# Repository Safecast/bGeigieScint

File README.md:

# bGeigieScint

**bGeigieScint** is a compact radiation detection board featuring a Silicon Photomultiplier (SiPM) based sensor system with integrated high-voltage generation, analog signal processing, and USB connectivity.

## 📋 Features

- **Microcontroller**: ATSAML21G18B (ARM Cortex-M0+, 256KB Flash, 32KB RAM)
- **SiPM Interface**: Complete analog frontend with adjustable HV bias (30-70V)
- **Power Management**: Multi-rail power supply (3.3V, 3.0V, Vload, Vbias)
- **Connectivity**: USB-C interface with ESD protection
- **Debug**: 10-pin J-LINK SWD interface + 18 test points
- **Expansion**: Multiple GPIO headers for external interfaces
- **Compact**: 40mm × 100mm 4-layer PCB

## 🔧 Hardware Specifications

### Main Components

| Component | Part Number | Function |
|-----------|-------------|----------|
| MCU | ATSAML21G18B-AUT | Main microcontroller (48-pin QFN) |
| USB | USB3.1C16PFSMT | USB-C connector (USB 2.0) |
| LDO 3.3V | XC6209F332MR-G | Main 3.3V regulator |
| LDO 3.0V | TPS7A2030PDBVR | 3.0V rail for analog |
| LDO Vload | LT3014BHVES5 | Low-noise LDO for HV control |
| OpAmp | OPA357AIDBVR | Shaper amplifier |
| Comparator | TLV3201AIDBVT | Fast comparator |
| Latch | MC14043BDR2G | Digital latch for triggering |

### SiPM Sensor

- **Part Number**: AFBR-S4N44P014M (Broadcom)
- **Type**: NUV-HD Silicon Photomultiplier
- **Active Area**: 4×4 mm²
- **Spectral Range**: 350-900 nm (peak sensitivity ~420 nm)
- **Datasheet**: [AFBR-S4N44P014M Documentation](https://docs.broadcom.com/doc/AFBR-S4N44P014M-NUV-MT-Silicon-Photomultiplier)

### Scintillator Crystal

- **Material**: CsI(Tl) - Cesium Iodide doped with Thallium
- **Dimensions**: 10 mm × 10 mm × 20 mm
- **Emission Peak**: ~550 nm (matches SiPM sensitivity)
- **Application**: Gamma ray detection coupled to SiPM

### Power Supply

- **Input**: 4.5-6V via USB-C or external connector
- **Output Rails**:
  - 3.3V @ up to 200mA (digital)
  - 3.0V @ up to 100mA (analog)
  - Vload (adjustable)
  - Vbias: 30-70V @ low current (SiPM bias)

### HV Generation

The board features an integrated **boost converter + linear regulator** topology for SiPM bias generation:

- **Boost Stage**: PWM-controlled (L1 10mH inductor, Q3 P-FET, D9 Schottky)
- **Regulation**: LT3014 ultra-low-noise LDO
- **Control**: MCU DAC output (PA02_DAC_HV) sets target voltage
- **Monitoring**: Comparator feedback (PB10_HV_COMP_OUT)
- **Output**: Adjustable 30-70V Vbias for SiPM

## 📁 Project Structure

```
bGeigieScint/
├── bGeigieScint/
│   ├── bGeigieScint.kicad_pro       # KiCad project file
│   ├── bGeigieScint.kicad_sch       # Schematic (organized in functional blocks)
│   ├── bGeigieScint.kicad_pcb       # PCB layout (4-layer, 40×100mm)
│   ├── bGeigieScint-backups/        # Automatic backups
│   ├── firmware/                    # Firmware source code
│   │   └── PomeloCore/              # Main firmware project
│   ├── bootloader/                  # Bootloader files
│   │   └── uf2-samd21/              # UF2 bootloader for SAMD21
│   ├── v1_2/                        # Version 1.2 reference files
│   │   ├── schematic/               # V1.2 schematic PDF
│   │   ├── firmware/                # V1.2 firmware
│   │   └── bootloader/              # V1.2 bootloader
│   ├── Images/                      # Project images and photos
│   └── Misc Docs/                   # Additional documentation
├── BOM.csv                          # Bill of Materials
├── Python scripts (*.py)            # KiCad automation scripts
└── README.md                        # This file
```

## 🎨 Schematic Organization

The schematic is organized into **7 functional blocks**:

1. **USB & POWER INPUT**: USB-C interface, power connectors, reset button
2. **POWER MANAGEMENT**: LDOs, inductors, power distribution
3. **MCU CORE**: Microcontroller, crystal, decoupling
4. **ANALOG FRONTEND**: SiPM signal chain, opamps, comparators
5. **LOGIC & CONTROL**: Digital logic, latches, level shifters
6. **EXPANSION I/O**: Pin headers for external connections
7. **DEBUG & TEST**: J-LINK interface, test points

## 🔌 Pinout & Interfaces

### J-LINK Debug Header (10-pin)
```
1: VCC        2: SWDIO
3: GND        4: SWCLK
5: GND        6: SWO
7: NC         8: NC
9: GND       10: RESET
```

### Expansion Headers

- **H2, H3**: 7-pin GPIO expansion
- **H5**: 7-pin expansion with labeled signals
- **MEAS1**: 2-pin measurement header
- **P1, P2**: 2×2 power connectors (mirrored on Pomelo Physics board)

### Key Signals

| Signal | Description |
|--------|-------------|
| SiPM_A | SiPM analog input |
| Vbias | SiPM bias voltage output |
| SHAPER_OUT | Shaped pulse output |
| PA02_DAC_HV | HV control DAC output |
| PA10_PWM | Boost converter PWM |
| PB03_PEAKDET_EN | Peak detector enable |
| PA23_TRG_OUT | Trigger output |

## 📊 Version History

### V1.3 (Current)
**Major improvements over V1.2:**

✅ **Added (47 components)**:
- USB-C connector (USBC1)
- Reset button (BUT1)
- J-LINK debug header
- 18 test points (TP1-TP18)
- Additional transistors (Q4, Q5) and diodes (D6, D8, D10)
- 15 new resistors for better signal conditioning

✅ **Changed**:
- C44: 1uF → 4.7uF
- C45: 4.7uF → 1uF
- H2, H3: 6-pin → 7-pin headers (expanded)

✅ **Enhanced**:
- Better debugging capability
- Improved power filtering
- More flexible I/O expansion

### V1.2 (Legacy)
- Initial production version
- PDF schematic available in `v1_2/schematic/`

## 🚀 Getting Started

### Prerequisites

- **KiCad 9.0** or later
- Basic understanding of radiation detection and SiPM operation
- JTAG/SWD programmer (e.g., J-Link, ST-Link)

### Opening the Project

1. Clone this repository
2. Open `bGeigieScint/bGeigieScint.kicad_pro` in KiCad
3. The schematic shows functional blocks with dashed rectangles
4. The PCB has components organized by function

### Manufacturing

**PCB Specifications:**
- **Layers**: 4 (signal/GND/VCC/signal)
- **Dimensions**: 40mm × 100mm
- **Thickness**: 1.6mm
- **Copper**: 35μm (1oz) on all layers
- **Min Track/Space**: 0.15mm / 0.15mm (for 0805 components)
- **Finish**: HASL or ENIG recommended
- **Solder Mask**: Green (top and bottom)

**Assembly Notes:**
- Minimum component size: 0805 for passives
- QFN-48 MCU requires reflow soldering
- LDOs are SOT-23-5 packages
- Test points for easy debugging

## 📝 Design Notes

### Power Planes
- **Layer 1 (In1.Cu)**: GND plane - solid pour for low noise
- **Layer 2 (In2.Cu)**: VCC plane - split for 3.3V/3.0V rails

### Critical Traces
- Keep SiPM analog traces short and shielded
- HV traces (Vbias) should be isolated from digital signals
- Crystal traces should be short with GND guard ring

### Component Placement
Components are organized into functional blocks:
- Power supply on left side
- MCU in center
- Analog section on right
- Digital logic bottom-right

## 🔬 Applications

- Radiation detection and measurement
- Scintillation counting
- Environmental monitoring
- Educational radiation physics
- DIY Geiger counter replacement with better sensitivity

## 👥 Credits

**Original Designer**: Mihai Cuciuc (M. Cuciuc)
**Original Repository**: [github.com/mihaicuciuc/pomelo](https://github.com/mihaicuciuc/pomelo)
**Organization**: Safecast
**Date**: 2024-2025

Safecast appreciates the great work that Mihai has done and made publicly available. This project builds upon the original Pomelo design.

## 📄 License

- **Hardware Design** (schematics, PCB layouts, design files): [CC0 1.0 Universal](https://creativecommons.org/publicdomain/cc0/1.0/)
- **Firmware and Software**: [MIT License](https://opensource.org/licenses/MIT)

This project is completely open source and free to use, modify, and distribute.

## 🤝 Contributing

Contributions are welcome! Please:

1. Fork the repository
2. Create a feature branch
3. Make your changes
4. Submit a pull request

For major changes, please open an issue first to discuss what you would like to change.

## 📞 Support

- **Project Page**: [Pomelo on Crowd Supply](https://www.crowdsupply.com/pomelo-instrumentation/pomelo)
- **Safecast**: [https://safecast.org](https://safecast.org)
- Report issues through the repository's issue tracker

## ⚠️ Safety Warning

This board generates **high voltage** (up to 70V) for SiPM biasing. Handle with care:
- Do not touch HV traces while powered
- Use proper ESD protection
- Follow safe electronics handling practices
- Designed for educational and research purposes

---

**Made with ❤️ for the radiation detection community**

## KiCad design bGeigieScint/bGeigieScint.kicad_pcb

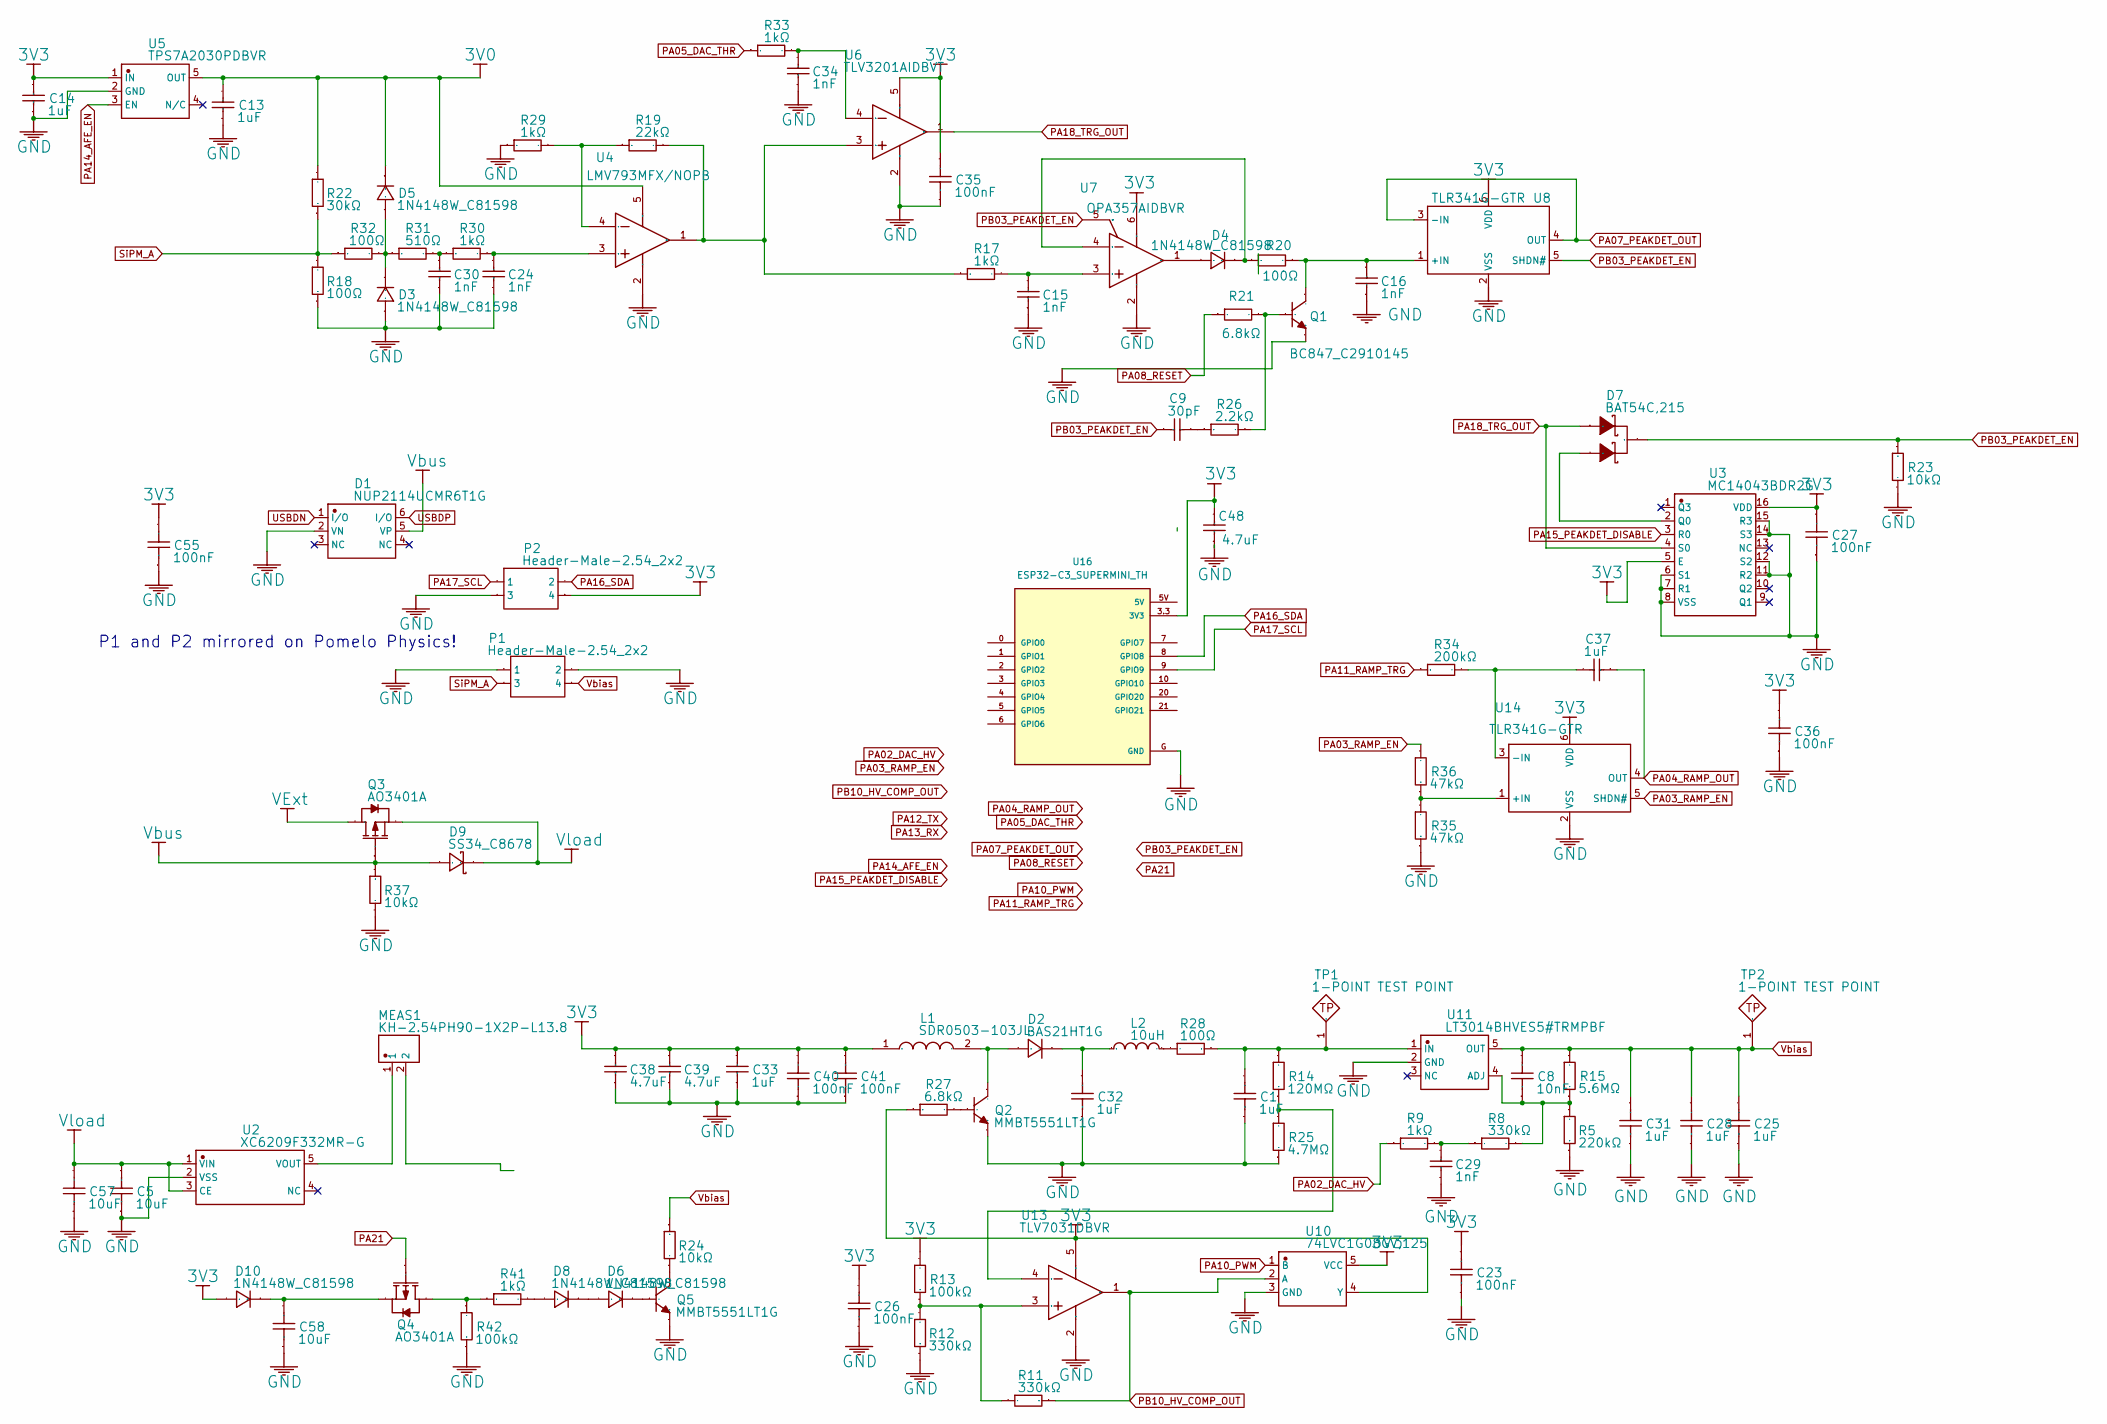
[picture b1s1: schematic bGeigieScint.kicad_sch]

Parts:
C1, C32: 1uF; C_0805_2012Metric; Manufacturer Part GRM55DR72D105KW01L
C5, C57, C58: 10uF; C_1206_3216Metric; Manufacturer Part CL10A106KP8NNNC
C8: 10nF; C_0805_2012Metric; Manufacturer Part 12062C103KAT2A
C9: 30pF; C_0805_2012Metric; Manufacturer Part 0603CG300J500NT
C13, C14, C33, C37: 1uF; C_0805_2012Metric; Manufacturer Part CL10A105KB8NNNC
C15, C16, C24, C29, C30, C34: 1nF; C_0805_2012Metric; Manufacturer Part CL10B102KB8NNNC
C23, C26, C27, C35, C36, C40, C41, C55: 100nF; C_0805_2012Metric; Manufacturer Part CC0603KRX7R9BB104
C25, C28, C31: 1uF; C_0805_2012Metric; Manufacturer Part 08051C105KAT2A
C38, C39: 4.7uF; C_1812_4532Metric; Manufacturer Part 1206B475K500NT
C48: 4.7uF; C_0805_2012Metric; Manufacturer Part CL10A475KO8NNNC
D1: NUP2114UCMR6T1G; SO-8_3.9x4.9mm_P1.27mm; Manufacturer Part NUP2114UCMR6T1G
D2: BAS21HT1G; SOT-23; Manufacturer Part BAS21HT1G
D3, D4, D5, D6, D8, D10: 1N4148W_C81598; D_SOD-123; Manufacturer Part 1N4148W
D7: BAT54C,215; SOT-23; Manufacturer Part BAT54C,215
D9: SS34_C8678; D_SMA; Manufacturer Part SS34
L1: SDR0503-103JL; L_0805_2012Metric
L2: 10uH; L_1210_3225Metric; Manufacturer Part SDFL1608S100KTF
MEAS1: KH-2.54PH90-1X2P-L13.8; PinHeader_1x02_P2.54mm_Vertical; Manufacturer Part KH-2.54PH90-1X2P-L13.8
P1, P2: Header-Male-2.54_2x2; PinHeader_2x02_P2.54mm_Vertical; Manufacturer Part 2.54-2*2P针
Q1: BC847_C2910145; SOT-23; Manufacturer Part BC847
Q2, Q5: MMBT5551LT1G; SOT-23; Manufacturer Part MMBT5551LT1G
Q3, Q4: AO3401A; SOT-23; Manufacturer Part AO3401A
R5: 220kΩ; R_0805_2012Metric; Manufacturer Part 0603WAF2203T5E
R8, R11, R12: 330kΩ; R_0805_2012Metric; Manufacturer Part 0603WAF3303T5E
R9, R17, R29, R30, R33, R41: 1kΩ; R_0805_2012Metric; Manufacturer Part 0603WAF1001T5E
R13, R42: 100kΩ; R_0805_2012Metric; Manufacturer Part 0603WAF1003T5E
R14: 120MΩ; R_0805_2012Metric; Manufacturer Part 0603WAF4704T5E
R15: 5.6MΩ; R_0805_2012Metric; Manufacturer Part 0603WAF5604T5E
R18, R20, R28, R32: 100Ω; R_0805_2012Metric; Manufacturer Part 0603WAF1000T5E
R19: 22kΩ; R_0805_2012Metric; Manufacturer Part 0603WAF2202T5E
R21, R27: 6.8kΩ; R_0805_2012Metric; Manufacturer Part 0603WAF6801T5E
R22: 30kΩ; R_0805_2012Metric; Manufacturer Part 0603WAF3002T5E
R23, R24, R37: 10kΩ; R_0805_2012Metric; Manufacturer Part 0603WAF1002T5E
R25: 4.7MΩ; R_0805_2012Metric; Manufacturer Part 0603WAF4704T5E
R26: 2.2kΩ; R_0805_2012Metric; Manufacturer Part 0603WAF2201T5E
R31: 510Ω; R_0805_2012Metric; Manufacturer Part 0603WAF5100T5E
R34: 200kΩ; R_0805_2012Metric; Manufacturer Part 0603WAF2003T5E
R35, R36: 47kΩ; R_0805_2012Metric; Manufacturer Part 0603WAF4702T5E
TP1, TP2: 1-POINT TEST POINT; TestPoint_Pad_D1.5mm
U2: XC6209F332MR-G; SOT-23-5; Manufacturer Part XC6209F332MR-G
U3: MC14043BDR2G; SOIC-16_3.9x9.9mm_P1.27mm; Manufacturer Part MC14043BDR2G
U4: LMV793MFX/NOPB; MSOP-8_3x3mm_P0.65mm; Manufacturer Part LMV793MFX/NOPB
U5: TPS7A2030PDBVR; SOT-23-5; Manufacturer Part TPS7A2030PDBVR
U6: TLV3201AIDBVT; SOT-23-5; Manufacturer Part TLV3201AIDBVT
U7: OPA357AIDBVR; SOT-23-5; Manufacturer Part OPA357AIDBVR
U8, U14: TLR341G-GTR; SOT-23-6; Manufacturer Part TLR341G-GTR
U10: 74LVC1G08GV,125; SOT-353_SC-70-5; Manufacturer Part 74LVC1G08GV,125
U11: LT3014BHVES5#TRMPBF; SOT-23-5; Manufacturer Part LT3014BHVES5#TRMPBF
U13: TLV7031DBVR; SOT-23-5; Manufacturer Part TLV7031DBVR
U16: ESP32-C3_SUPERMINI_TH; MODULE_ESP32-C3_SUPERMINI_TH

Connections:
3V0: C13.2, D5.1 (K), R22.2, U4.5 (V+), U5.5 (OUT)
3V3: C14.2, C23.2, C26.2, C27.2, C33.2, C35.2, C36.2, C38.2, C39.2, C40.2, C41.2, C48.2, C55.2, D10.2 (A), L1.1, P2.4, R13.2, R27.1, U3.5 (E), U3.16 (VDD), U5.1 (IN), U6.5 (VCC), U7.6 (V+), U8.6 (VDD), U10.4 (Y), U10.5 (VCC), U13.5 (VCC), U14.6 (VDD), U16.3.3 (3V3); also elsewhere on the board
GND: C1.1, C5.1, C13.1, C14.1, C15.1, C16.1, C23.1, C24.1, C25.1, C26.1, C27.1, C28.1, C29.1, C30.1, C31.1, C32.1, C33.1, C34.1, C35.1, C36.1, C38.1, C39.1, C40.1, C41.1, C48.1, C55.1, C57.1, C58.1, D1.2 (VN), D3.2 (A), P1.1, P1.2, P2.3, Q1.2 (E), Q2.2 (E), Q5.2 (E), R5.1, R12.1, R18.1, R23.2, R25.1, R29.1, R35.1, R37.2, R42.1, U2.2 (VSS), U3.6 (S1), U3.7 (R1), U3.8 (VSS), U3.11 (R2), U3.12 (S2), U3.14 (S3), U3.15 (R3), U4.2 (V-), U5.2 (GND), U6.2 (GND), U7.2 (V-), U8.2 (VSS), U10.3 (GND), U11.2 (GND), U13.2 (VEE), U14.2 (VSS), U16.G (GND); also elsewhere on the board
unnamed: C9.2, R26.1
unnamed: C29.2, R8.1, R9.2
unnamed: C30.2, R30.1, R31.2
unnamed: D2.2 (A), L1.2, Q2.3 (C)
unnamed: C32.2, D2.1 (C), L2.1
unnamed: D3.1 (K), D5.2 (A), R31.1, R32.2
unnamed: D4.2 (A), U7.1 (OUT)
unnamed: D4.1 (K), R20.1, U7.4 (IN-)
unnamed: D6.2 (A), D8.1 (K)
unnamed: D6.1 (K), Q5.1 (B)
unnamed: D8.2 (A), R41.2
unnamed: C58.2, D10.1 (K), Q4.2 (S)
unnamed: L2.2, R28.2
unnamed: Q1.1 (B), R21.2, R26.2
unnamed: C16.2, Q1.3 (C), R20.2, U8.1 (+IN)
unnamed: Q2.1 (B), R27.2
unnamed: Q4.3 (D), R41.1, R42.2
unnamed: Q5.3 (C), R24.2
unnamed: MEAS1.1, U2.5 (VOUT)
unnamed: D7.2 (A), U3.2 (Q0)
unnamed: C24.2, R30.2, U4.3 (+IN)
unnamed: R19.1, R29.2, U4.4 (-IN)
unnamed: R17.1, R19.2, U4.1 (OUTPUT), U6.3 (VIN+)
unnamed: C34.2, R33.2, U6.4 (VIN-)
unnamed: C15.2, R17.2, U7.3 (IN+)
unnamed: C8.1, R5.2, R8.2, R15.1, U11.4 (ADJ)
unnamed: C1.2, R14.2, R28.1, TP1.1, U11.1 (IN)
unnamed: R11.2, R12.2, R13.1, U13.3 (IN+)
unnamed: R14.1, R25.2, U13.4 (IN-)
unnamed: R35.2, R36.1, U14.1 (+IN)
unnamed: C37.2, R34.2, U14.3 (-IN)
PA02_DAC_HV: R9.1
PA03_RAMP_EN: R36.2, U14.5 (SHDN#)
PA04_RAMP_OUT: C37.1, U14.4 (OUT)
PA05_DAC_THR: R33.1
PA07_PEAKDET_OUT: U8.3 (-IN), U8.4 (OUT)
PA08_RESET: R21.1
PA10_PWM: U10.1 (B)
PA11_RAMP_TRG: R34.1
PA14_AFE_EN: U5.3 (EN)
PA15_PEAKDET_DISABLE: U3.3 (R0)
PA16_SDA: P2.2, U16.8 (GPIO8)
PA17_SCL: P2.1, U16.9 (GPIO9)
PA18_TRG_OUT: D7.1 (A), U3.4 (S0), U6.1 (OUT)
PA21: Q4.1 (G)
PB03_PEAKDET_EN: C9.1, D7.3 (K), R23.1, U7.5 (ENABLE), U8.5 (SHDN#)
PB10_HV_COMP_OUT: R11.1, U10.2 (A), U13.1 (OUT)
SiPM_A: P1.3, R18.2, R22.1, R32.1
USBDN: D1.1 (I/O)
USBDP: D1.6 (I/O)
VExt: Q3.3 (D); also elsewhere on the board
Vbias: C8.2, C25.2, C28.2, C31.2, P1.4, R15.2, R24.1, TP2.1, U11.5 (OUT)
Vbus: D1.5 (VP), D9.2 (A), Q3.1 (G), R37.1
Vload: C5.2, C57.2, D9.1 (K), Q3.2 (S), U2.1 (VIN), U2.3 (CE)

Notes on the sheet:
P1 and P2 mirrored on Pomelo Physics!

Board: 4 copper layers, 100 parts (0 on the bottom side), 51 nets, no tracks yet.

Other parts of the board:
C56: 100nF; C_0805_2012Metric
R39: 27kΩ; R_0805_2012Metric
U12: TXU0202DCUR; VSSOP-8_2.3x2mm_P0.5mm
U15: 803-87-006-10-001101; PinSocket_1x06_P2.54mm_Vertical

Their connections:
3V3: R39.1, U12.2 (VCCA), U15.4; also elsewhere on the board
GND: C56.1, U12.5 (GND), U15.1; also elsewhere on the board
PA13_RX: R39.2, U12.1 (A2)
RX: U12.8 (B2), U15.3
TX: U12.6 (B1), U15.5
VExt: U15.2; also elsewhere on the board
VL: C56.2, U12.3 (OE), U12.7 (VCCB), U15.6

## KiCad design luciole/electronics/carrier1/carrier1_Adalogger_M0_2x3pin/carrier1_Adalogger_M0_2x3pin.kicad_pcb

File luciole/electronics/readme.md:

# Scintillator PCBs

In this architecture, there are two printed circuit boards. A small one, the readout, is nested inside the hood covering the scintillator. The second is the carrier on which the scintillator is mounted with headers protruding from the bottom of the hood.

## Updates

* 2026-05-06 Hood base for readout1_A booked to be 3D printed at library
* 2026-04-28 readout1_A sent to JLCPCB

## Readout PCB - Direct Connection to SiPM

The readout carries the SiPM itself as well as the anode resistor and the decoupling capacitor on the bias supply. The two 3-pos headers are meant to protrude from the bottom of the hood base, to be soldered into the carrier. The readout also carries a temperature sensor used by the firmware for calibration.

## Versions

### Version `readout1`: Two 3-pin headers

The PCB placement of the SiPM is at the 0,0 origin. The headers and mounting holes are symmetric along the Y-axis. With two headers, the scintillator hood must be vertical on the carrier.

### Version `readout2`: A single 6-pin header

(Not started yet). This version allows for more mounting flexibility for the scintillator hood -- laterally or vertically. However, it complicates the PCB layout and the base of the hood.

## Carrier PCB - Carries the scintillator and interprets the pulses 

The carrier PCB receives the readout PCB and hood through the headers protruding from the bottom, and conditions the scintillator output through amplifiers, comparators and integrators. The signals are digitized by either a standalone high speed ADC, or the ADC built into the microcontroller -- both approaches will be tried. Initially, the microcontroller  is the Adafruit Feather M0 Adalogger, mostly because it was already on hand though it seems to have the necessary capabilities. It can also be powered from a 3.7V Li-Ion battery.

### Version `carrier1_Adalogger_M0_2x3pin`: Two 3-pin headers

The hood has two 3-pos headers. The microcontroller is the Adafruit Feater M0 Adalogger. Analgog signal conditioning parts TBD -- need sufficiently high speed and low noise op-amps and ADC.

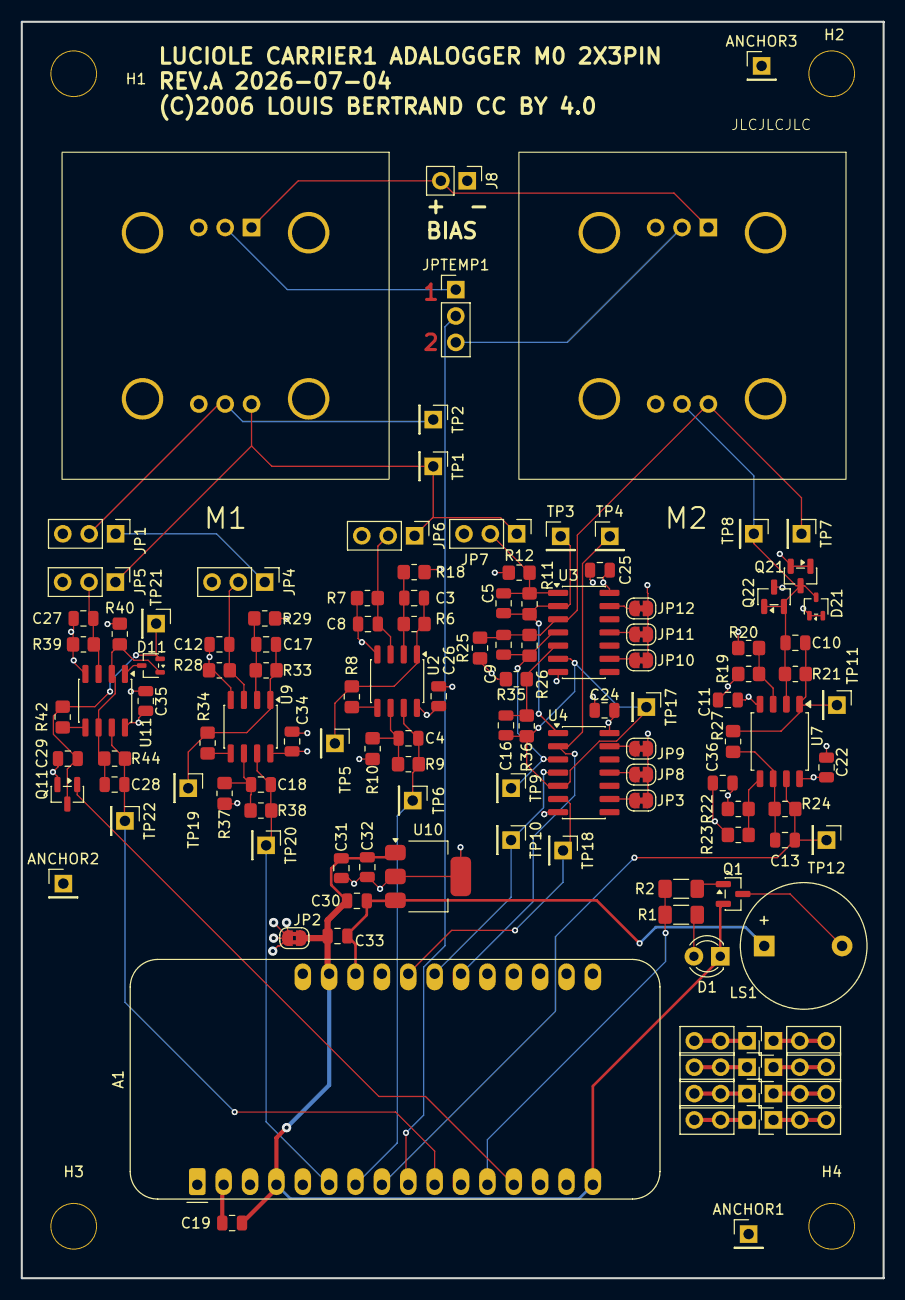
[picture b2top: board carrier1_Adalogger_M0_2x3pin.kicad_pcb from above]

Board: 4 copper layers, 83.0 x 121.0 mm, 123 parts (0 on the bottom side), 63 nets.

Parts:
A1: Adafruit_Feather_M0_Adalogger; Adafruit_Feather
ANCHOR1, ANCHOR2, ANCHOR3: Conn_01x01_Pin; PinHeader_1x01_P2.54mm_Vertical
C3, C4, C5, C8, C9, C10, C12, C13, C16, C17, C18: 10pf; C_0805_2012Metric
C11, C36: 100nf; C_0805_2012Metric
C19, C22, C24, C25, C26, C30, C32, C33, C34, C35: 100n; C_0805_2012Metric
C27, C28: 10pF; C_0805_2012Metric
C29: 10nF; C_0805_2012Metric
C31: 1u; C_0805_2012Metric
D1: LED BLUE; LED_D3.0mm_Clear
D11, D21: BAT54SW; SOT-323_SC-70
H1, H2, H3, H4: MountingHole; MountingHole_4.3mm_M4
J8: Conn_01x02_Pin; PinHeader_1x02_P2.54mm_Vertical
JP1, JP4, JP5, JP6, JP7: Jumper_3_Open; PinHeader_1x03_P2.54mm_Vertical
JP2: SolderJumper_2_Bridged; SolderJumper-2_P1.3mm_Bridged2Bar_RoundedPad1.0x1.5mm
JP3, JP8, JP9, JP10, JP11, JP12: SolderJumper_2_Bridged; SolderJumper-2_P1.3mm_Bridged_RoundedPad1.0x1.5mm
JPTEMP1: Jumper_3_Open; PinHeader_1x03_P2.54mm_Vertical
LS1: CPT-1207-3TH; Buzzer_12x9.5RM7.6
M1, M2: Readout1 2x3 pins 8x8 holes
PROTO1, PROTO2, PROTO3, PROTO4, PROTO5, PROTO6, PROTO7, PROTO8: Conn_01x03_Pin; PinHeader_1x03_P2.54mm_Vertical
Q1, Q21, Q22: MMBT3904; SOT-23
Q11: BSS138; SOT-23
R1: 220; R_1206_3216Metric_Pad1.30x1.75mm_HandSolder
R2: 1k0; R_1206_3216Metric_Pad1.30x1.75mm_HandSolder
R6, R8, R9, R10, R18, R21, R27, R29, R33, R34, R37, R38, R40, R42, R44: 500; R_0805_2012Metric_Pad1.20x1.40mm_HandSolder
R7, R28, R39: TBD; R_0805_2012Metric_Pad1.20x1.40mm_HandSolder
R11, R12, R25, R26, R35, R36: 1M0; R_0805_2012Metric_Pad1.20x1.40mm_HandSolder
R19, R20, R22, R23: 1k0; R_0805_2012Metric_Pad1.20x1.40mm_HandSolder
R24: 5k1; R_0805_2012Metric_Pad1.20x1.40mm_HandSolder
TP1, TP2, TP3, TP4, TP5, TP6, TP7, TP8, TP9, TP10, TP11, TP12, TP17, TP18, TP19, TP20, TP21, TP22: Conn_01x01_Pin; PinHeader_1x01_P2.54mm_Vertical
U2, U9, U11: OPA2354xxD; SO-8_3.9x4.9mm_P1.27mm
U3: 74HCU04; SO-14_3.9x8.65mm_P1.27mm
U4: 74HC14; SO-14_3.9x8.65mm_P1.27mm
U7: OPA2354xxD; SOIC-8_5.3x5.3mm_P1.27mm
U10: AZ1117-3.3; SOT-223-3_TabPin2

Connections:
+3V3: A1.2 (3V3), C11.2, C19.1, C22.1, C24.1, C25.1, C26.1, C31.1, C32.1, C34.1, C35.1, C36.2, M1.3 (+3V3), M2.3 (+3V3), R19.1, R22.2, U2.8 (V+), U3.14 (VCC), U4.14 (VCC), U7.8 (V+), U9.8 (V+), U10.2 (VO), U11.8 (V+)
+5V: A1.26 (USB), C30.1, C33.1, LS1.1, U10.3 (VI)
+BIAS: J8.2, M1.1 (+BIAS), M2.1 (+BIAS)
ANODE1: JP1.1 (A), JP4.1 (A)
ANODE2: C10.1, D21.3 (COM), M2.5 (ANODE), Q21.3 (C), Q22.1 (B), Q22.2 (E), R21.1, TP8.1 (Pin_1_1), U7.2 (-)
DETECTED: A1.12 (MOSI/D23), R1.1, R2.1
FAST1: JP5.1 (A), JP6.1 (A), JP7.1 (A), M1.6 (FAST), TP1.1 (Pin_1_1)
FAST2: C9.1, M2.6 (FAST), R25.2, R26.1, TP7.1 (Pin_1_1), U3.3
FAST3: C16.1, R35.2, R36.1, U3.5
FASTAMPOUT1: A1.7 (A2), C4.2, R9.2, TP6.1 (Pin_1_1), U2.7
FASTPULSE1: A1.22 (D10), TP4.1 (Pin_1_1), U4.2
FASTPULSE2: A1.23 (D11), TP10.1 (Pin_1_1), U4.4
FASTPULSE3: A1.24 (D12), TP18.1 (Pin_1_1), U4.6
GND: A1.4 (GND), A1.16 (GND), A1.27 (EN), C19.2, C30.2, C31.2, C32.2, C33.2, D1.1 (K), JP2.2 (B), Q1.2 (E), U10.1 (GND)
GNDA: ANCHOR1.1 (Pin_1_1), ANCHOR2.1 (Pin_1_1), ANCHOR3.1 (Pin_1_1), C8.1, C11.1, C12.1, C22.2, C24.2, C25.2, C26.2, C27.1, C29.1, C34.2, C35.2, C36.1, D21.1 (A), D21.2 (K), J8.1, JP1.3 (B), JP2.1 (A), JP3.1 (A), JP4.3 (B), JP5.3 (B), JP6.3 (B), JP7.3 (B), JP8.1 (A), JP9.1 (A), JP10.1 (A), JP11.1 (A), JP12.1 (A), M1.4 (GND), M2.4 (GND), Q11.2 (S), Q21.1 (B), Q21.2 (E), Q22.3 (C), R7.2, R10.1, R12.1, R18.1, R20.2, R23.1, R25.1, R28.2, R29.1, R35.1, R37.1, R39.2, R40.1, U2.4 (V-), U3.7 (GND), U4.7 (GND), U7.4 (V-), U9.4 (V-), U11.4 (V-)
unnamed: D1.2 (A), R1.2
unnamed: C28.1, D11.1 (A), R40.2, R44.1, U11.2 (-), U11.6 (-)
unnamed: D11.3 (COM), U11.1
unnamed: C29.2, D11.2 (K), Q11.3 (D), R42.1, TP21.1 (Pin_1_1)
unnamed: JP1.2 (C), M1.5 (ANODE), TP2.1 (Pin_1_1)
unnamed: JP3.2 (B), U4.9
unnamed: C12.2, JP4.2 (C), R28.1, U9.3 (+)
unnamed: C27.2, JP5.2 (C), R39.1, U11.3 (+)
unnamed: C8.2, JP6.2 (C), R7.1, U2.3 (+)
unnamed: C5.1, JP7.2 (C), R11.1, R12.2, U3.1
unnamed: JP8.2 (B), U4.11
unnamed: JP9.2 (B), U4.13
unnamed: JP10.2 (B), U3.9
unnamed: JP11.2 (B), U3.11
unnamed: JP12.2 (B), U3.13
unnamed: PROTO1.1, PROTO1.2, PROTO1.3
unnamed: PROTO2.1, PROTO2.2, PROTO2.3
unnamed: PROTO3.1, PROTO3.2, PROTO3.3
unnamed: PROTO4.1, PROTO4.2, PROTO4.3
unnamed: PROTO5.1, PROTO5.2, PROTO5.3
unnamed: PROTO6.1, PROTO6.2, PROTO6.3
unnamed: PROTO7.1, PROTO7.2, PROTO7.3
unnamed: PROTO8.1, PROTO8.2, PROTO8.3
unnamed: Q1.1 (B), R2.2
unnamed: LS1.2, Q1.3 (C)
unnamed: C5.2, R11.2, TP3.1 (Pin_1_1), U3.2, U4.1
unnamed: C3.2, R6.2, R8.1, TP5.1 (Pin_1_1), U2.1
unnamed: C9.2, R26.2, TP9.1 (Pin_1_1), U3.4, U4.3
unnamed: C10.2, R21.2, R27.1, TP11.1 (Pin_1_1), U7.1
unnamed: C16.2, R36.2, TP17.1 (Pin_1_1), U3.6, U4.5
unnamed: C17.2, R33.2, R34.1, TP19.1 (Pin_1_1), U9.1
unnamed: C3.1, R6.1, R18.2, U2.2 (-)
unnamed: R8.2, U2.5 (+)
unnamed: C4.1, R9.1, R10.2, U2.6 (-)
unnamed: R19.2, R20.1, U7.3 (+)
unnamed: R22.1, R23.2, U7.5 (+)
unnamed: C13.1, R24.1, R27.2, U7.6 (-)
unnamed: C17.1, R29.2, R33.1, U9.2 (-)
unnamed: R34.2, U9.5 (+)
unnamed: C18.1, R37.2, R38.1, U9.6 (-)
unnamed: R42.2, U11.5 (+)
PEAKHOLDOUT1: A1.10 (A5), C28.2, R44.2, TP22.1 (Pin_1_1), U11.7
PEAKRESET: A1.13 (MISO/D22), Q11.1 (G)
TEMP: A1.9 (A4), JPTEMP1.2 (C)
TEMP1: JPTEMP1.1 (A), M1.2 (TEMP)
TEMP2: JPTEMP1.3 (B), M2.2 (TEMP)
TIAMPOUT2: A1.8 (A3), C13.2, R24.2, TP12.1 (Pin_1_1), U7.7
VOLTAMPOUT1: A1.6 (A1), C18.2, R38.2, TP20.1 (Pin_1_1), U9.7

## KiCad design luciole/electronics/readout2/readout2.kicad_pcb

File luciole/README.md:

# Projet Luciole

A low cost radiation detection and measurement spectrometer for fixed location monitoring and reporting using a scintillator crystal and silicon photomultiplier. Une luciole serait un peu comme les petits éclairs de rayonnement dans le scintillateur.

## Functional requirements
* Scintillation detector (polymer or inorganic crystal)
* Sensitivity to gamma equal to or better than LND7317 G-M tube (beta optional)
* Temperature compensated measurements
* Communicate over WiFi in-house, optional cellular or satellite (Blues.io, brioconcept.com)
* Measurement uploads in Safecast format (existing LOG or new spectrum format)
* Low power with battery backup
* Easy to read display
* Simple UI for inexperienced users
* Touch OLED display, on-screen buttons
* Self calibrating or simple calibration procedure
* Not ruggedized, indoor use only
* Off-the-shelf case (Hammond, Takachi, etc.) or 3D printed
* USB-C charging and programming
* Build as a kit with minimal soldering

## Non-functional requirements
* Cost goal is sub CA$250.
* Parts reliably available from distribution

## Scintillators

Plastic (organic) scintillators are rugged and expected to be cheaper than inorganic crystals. They do not suffer from the limitations of some inorganic crystals, such as hygroscopic (absorb moisture) and cleavages.

### Possible sources

OST Photonics (China)
https://www.ostphotonics.com/products/sp101-plastic-scintillators.html
Do they offer off-the-shelf parts?

EPIC Crystal Co (China)
Online retail of organic and inorganic scintillators.

Luxium (USA)
Does not deal with less than minimum order USD3,000.

Eljen (USA)
Emailed Apr 14 asking about small quantities. No response. Abandon.

# Project structure

The prototype is more of a proof of concept than the precursor to a production device. It's a "throw it all at the wall to see what sticks" situation.

## Scintillator readout board
Readout is a small PCB holds a 6x6mm^2 silicon photomultiplier (SiPM). The device chosen for the first pass is OnSemi 60035 C-Series SiPM. The C-Series has an extra terminal, called Fast, that provides a voltage pulse proportional to the detection current. The other components on the board are a quench resistor, a power supply decoupling capacitor and an IC temperature sensor. Communication with the main board is through a pair of 3-pin headers.

Readout is packaged in a 3D printed enclosure consisting of a base and a hood. When assembled, the base and the hood block external light and hold the scintillator in place on the SiPM. The SiPM is coupled to the scintillator with optically clear grease to remove any air gaps.

## Main board
The main board, carrier, accepts the readout module and amplifies the pulses enough for the microcontroller's ADC to digitize for further processing. Several detection and amplification approaches are implemented on the carrier1 board.

### Fast output amplifiers
The Fast terminal provides a voltage pulse proportional to the detection current. The pin is capacitor coupled to the diode array and the signal is suitable for a high input impedance amplifier. Two amplifier architectures are tried. 

1 - Quick-and-dirty amplifier using an unbuffered CMOS digital inverter with a feedback resistor, sending its output to a Schmitt trigger inverter. This combination is expect to provide the minimum detection, outputting pulses without energy measurement, the same as a Geiger-Muller detector.

2 - Voltage amplifier for the Fast output, providing peak pulse voltage proportional to the detected energy.

### Avalanche photodiode current amplifiers
The avalance current can be converted to a voltage pulse across the 50 ohm quench resistor in series between the SiPM anode and ground and measured after a conventional voltage amplifier.

The avalanche current can be amplified and converted to a voltage signal using a transimpedance amplifier (TIA) receiving the diode avalanche current pulse. The output is expected to be a pulse with height proportional to the detected particle energy. The pulse is integrated by a RC low pass filter to meet the relatively slow ADC acqisition time. It requires a different configuration of the SiPM, where the anode is connected directly to the op-amp minus terminal and the quench resistor R1 is not populated on the readout board.

### Peak and hold detector
A peak and hold detector on the Fast output can hold the pulse height steady during the ADC acquisition cycle. This is something that seems to work on physicsopenlab.org. A voltage amplifier amplifies the Fast output and drives a diode peak detector. The peak is held until the microcontroller can digitize the voltage, then the microcontroller resets the peak by turning on a MOSFET across the hold capacitor. This scheme may need the CMOS inverter to detect the pulse and initiate the microcontroller conversion cycle.
https://physicsopenlab.org/2017/11/28/front-end-electronics-for-sipm/

## Microcontroller
The MCU is a Adafruit Feather M0 Adalogger with a 128x64 monochrome OLED. It was chosen because it was in a parts bin on my workbench. However, it's a reasonable choice for memory, speed and a 12-bit ADC.

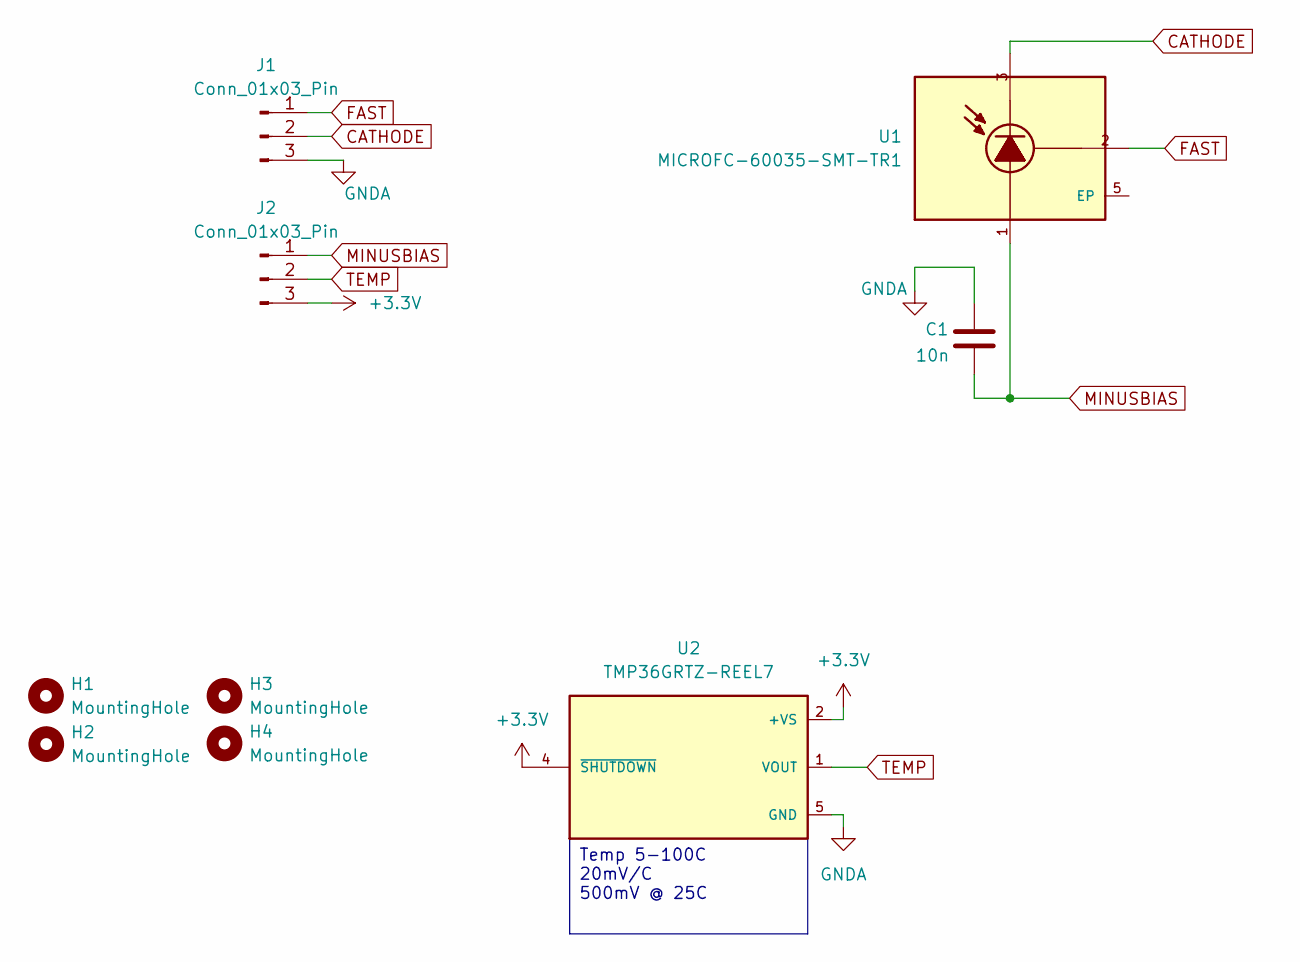
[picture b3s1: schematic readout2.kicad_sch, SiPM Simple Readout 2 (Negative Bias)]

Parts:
C1: 10n; C_1206_3216Metric_Pad1.33x1.80mm_HandSolder
H1, H2, H3, H4: MountingHole; MountingHole_3.2mm_M3_DIN965
J1, J2: Conn_01x03_Pin; PinHeader_1x03_P2.54mm_Vertical
U1: MICROFC-60035-SMT-TR1; XDCR_MICROFC-60035-SMT-TR1; PARTREV 31 JUL 2018
U2: TMP36GRTZ-REEL7; SOT95P280X145-5N; PARTREV H

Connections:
+3.3V: J2.3, U2.2 (+VS), U2.4 (~SHUTDOWN)
CATHODE: J1.2, U1.3
FAST: J1.1, U1.2
GNDA: C1.1, J1.3, U2.5 (GND)
MINUSBIAS: C1.2, J2.1, U1.1
TEMP: J2.2, U2.1 (VOUT)

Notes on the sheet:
Temp 5-100C 20mV/C 500mV @ 25C

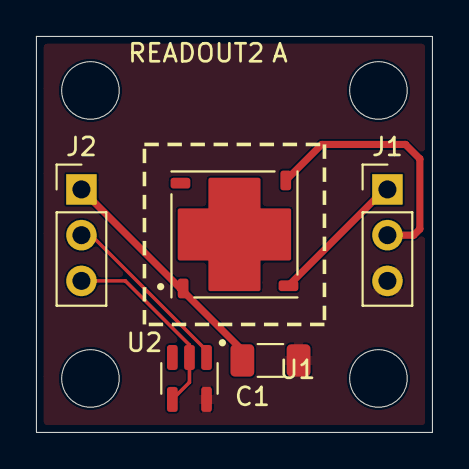
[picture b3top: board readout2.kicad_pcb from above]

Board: 4 copper layers, 22.0 x 22.0 mm, 9 parts (0 on the bottom side), 6 nets.

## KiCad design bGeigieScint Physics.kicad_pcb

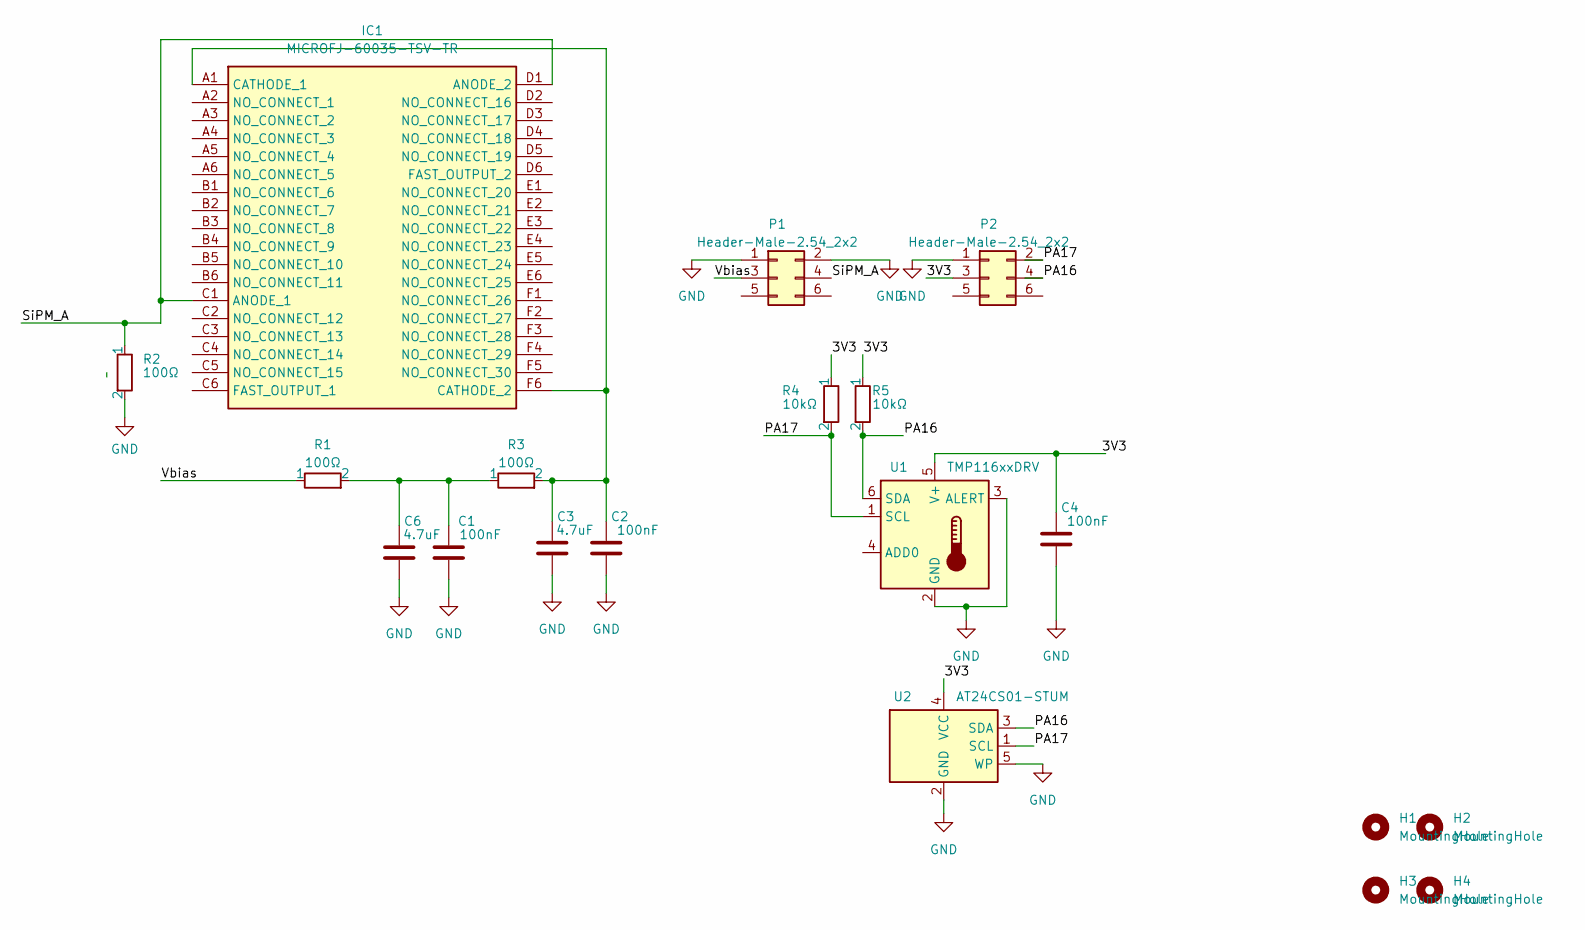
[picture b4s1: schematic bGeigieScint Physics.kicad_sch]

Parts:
C1, C2, C4: 100nF; C_0805_2012Metric
C3, C6: 4.7uF; C_0805_2012Metric
H1, H2, H3, H4: MountingHole; MountingHole_3.2mm_M3
IC1: MICROFJ-60035-TSV-TR; BGA36C100P6X6_613X613X67; Mouser Part Number 863-MFJ60035TSVTR
P1, P2: Header-Male-2.54_2x2; PinHeader_2x03_P2.54mm_Vertical_SMD
R1, R3: 100Ω; R_0805_2012Metric
R2: 100Ω
R4, R5: 10kΩ; R_0805_2012Metric
U1: TMP116xxDRV; WSON-6-1EP_2x2mm_P0.65mm_EP1x1.6mm
U2: AT24CS01-STUM; SOT-23-5

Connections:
/3V3: C4.1, P2.3, R4.1, R5.1, U1.5 (V+), U2.4 (VCC)
/PA16: P2.4, R5.2, U1.6 (SDA), U2.3 (SDA)
/PA17: P2.2, R4.2, U1.1 (SCL), U2.1 (SCL)
/SiPM_A: IC1.C1 (ANODE_1), IC1.D1 (ANODE_2), P1.4, R2.1
/Vbias: P1.3, R1.1
GND: C1.2, C2.2, C3.2, C4.2, C6.2, P1.1, P1.2, P2.1, R2.2, U1.2 (GND), U1.3 (ALERT), U2.2 (GND), U2.5 (WP)
unnamed: C1.1, C6.1, R1.2, R3.1
unnamed: C2.1, C3.1, IC1.A1 (CATHODE_1), IC1.F6 (CATHODE_2), R3.2

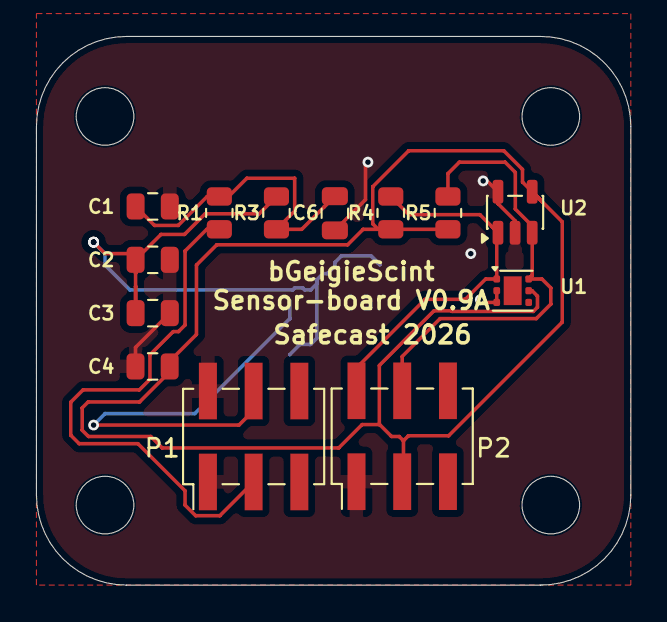
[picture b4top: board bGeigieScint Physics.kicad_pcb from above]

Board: 4 copper layers, 33.0 x 30.5 mm, 18 parts (1 on the bottom side), 8 nets.

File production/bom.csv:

Designator,Footprint,Quantity,Value,LCSC Part #
"C1, C2, C4",0805,3,100nF,
"C3, C6",0805,2,4.7uF,
IC1,BGA36C100P6X6_613X613X67,1,MICROFJ-60035-TSV-TR,
"P1, P2",PinHeader_2x02_P2.54mm_Vertical_SMD,2,Header-Male-2.54_2x2,
"R1, R3",0805,2,100Ω,
"R4, R5",0805,2,10kΩ,
U1,WSON-6-1EP_2x2mm_P0.65mm_EP1x1.6mm,1,TMP116xxDRV,
U2,SOT-23-5,1,AT24CS01-STUM,

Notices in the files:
README.md:
License: MIT
luciole/electronics/carrier1/carrier1_Adalogger_M0_2x3pin/carrier1_Adalogger_M0_2x3pin.kicad_pcb:
CC BY 4.0 https://creativecommons.org/licenses/by/4.0
(C)2006 LOUIS BERTRAND CC BY 4.0
luciole/electronics/readout2/firstattempt/readout2.kicad_sch:
CC-BY-4.0
